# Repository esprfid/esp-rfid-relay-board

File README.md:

# ESP-RFID Relay Board

This project is follow up for "ESP-RFID Board" but with few more options.

&nbsp;&nbsp;

## What is ESP-RFID Relay Board?
ESP-RFID Relay Board is tiny ESP12 module (ESP8266) board, designed with wiegand RFID readers in mind and [ESP-RFID Firmware](https://github.com/esprfid/esp-rfid)

* Small size factor, sometimes possible to glue it into existing readers.
* Single power source to power 12V/2A powers ESP12 module, RFID Wiegand Reader and magnetic lock for opening doors.
* Exposed programming pins for ESP8266
* Due to interesting hardware design, you get multiple possible setup options:
  * Forward Bell ringing on reader to MCU or pass it out of board
  * Track Door Status
  * Control reader’s status LED
  * Control reader’s status BUZZER sound
  * Power reader, lock and the board through single 12V, 2A PSU
  * Optionally power magnetic lock through external AC/DC PSU
  * Possible to use any kind and any type of wiegand readers
  * Enables you to make IOT Access System with very litle wiring
  * Fit in universal enclosures with DIN mount
* Opensource Hardware/Cloud RFID reader/Wifi RFID reader

## Wiring example:

&nbsp;&nbsp;

## RESET and FLASH Buttons
Same as for any other ESP8266 programmer where you need to put EPS8266 into a specific mode. If you want to upload your program, you would use this buttons to put ESP8266 into FLASH mode. Check programming procedure down.

## Reader 9 pin terminal
The reason for 9 pins is to cover the most complex wiegand reader i could fins on the market. Mostly they only have 5 or 6 wires but sometimes, they also have 9 wire versions.

**PINNAME**|**CONNECTION**|**DESCRIPTION**
:-----|:-----|:-----
**DO**|GPIO4|Wiegand data line **D0** (*)
**D1**|GPIO5|Wiegand data line **D1**. (*)
**WG**|GPIO0|Some readers have WG line which if HIGH/LOW can change Wiegand stream bits. Usually not very important!
**BUZ**|GPIO12|Almost always Wiegand RFID Readers have Buzzer line which can control piezo buzzer. Due to some inconsistency among readers, i was able to make it work only when i connect this line through 10K resistor and than control it with changing HIGH/LOW on that particular pin, depending what i want. IMPORTANT: **P3** Pad on the back of board, can make that line to be connected directly to GPIO or through 10k resistor. Check **P3** Pad explanation.
**LED**|GPIO15|Most Wiegand readers have RED/GREEN status LEDs. Some color is default and if the line is changed HIGH/LOW than the other color appears.
**GND**|GND|Planned for Wiegand RFID Reader GND.
**VIN**|VIN|Connected directly to board’s POWER terminal’s positive pole. (*)
**F2**|To BTN/IN terminal left pole or to  GPIO14 (**)|Rarely Wiegand RFID Readers incorporate one button which is often doorbell switch, but the version that i took as an example for this board has those wires. It’s simply the switch between F1/F2.
**F1**|To BTN/IN terminal right pole or to GPIO14 (**)|

## Screw Terminals On the bottom of ESP-RFID Relay Board

**TERMINAL NAME**|**DESCRIPTION**
:-----|:-----
**RPOW**|In case **RELAY-POWER** pad is connected, when relay connects the circuit, this terminal provides input voltage directly on it’s poles. So the door magnet lock can be powered directly through this terminal.
**RSW**|Since i used small signal relay, it had two sides so another side is also connecting at the same time when relay makes connection but it only cut circuit. So practical use for this terminal can be to power magnetic lock with external source and even AC so that you get buzzing sound when the lock opens and avoid jamming of the lock. (*)
**POWER 8V-12V**|This is the main power source and in some settings only power source that you need. Please provide minimum 2A if you also power magnetic lock and Wiegand RFID Reader from same source, through ESP-RFID Relay Board
**DOORSTAT**|This terminal was planned to accept door status magnet switch. It can be also repurposed since it’s just a "button" connected to **GPIO16**.
**BTN/IN**|Depending on **P1** and **P2** Pads connection, it can have different purposes.Check **P2/P3** pads description below.

## Configuration pads P1, P2, P3, RELAY-POWER, 5V/3V3

**PAD NAME**|**DESCRIPTION**
:-----|:-----
**P1**|**Options:** Connected poles **3** and **2** redirects **F1** on **RFID Reader Terminal** to **BTN/IN** right pole. Connected poles 3 and 1 and you will get **GPIO14** to be connected on left **BTN/IN** terminal, grounded with 10k resistor. Connected poles **2** and **1** and you will power pin **F1** on **RFID Reader Terminal** with **GPIO14** (*)
**P2**|**Options:** Connected poles **3** and **2** redirects **F2** on  RFID Reader Terminal to BTN/IN left pole. Connected poles 3 and 1 and you will get 3V3 on left pin of BTN/IN terminal. Connected poles **2** and **1** and you will power pin **F2** on **RFID Reader Terminal** with 3V3 (*)
**P3**|**Options:** Connected poles **1** and **2** redirects **BUZ** pin on **RFID Reader Terminal** and **GPIO12**. Connected poles **2** and **3** redirects **BUZ** pin on **RFID Reader Terminal** and **GPIO12** through 10K resistor.
**RELAY-POWER**| This pad is usually connected if you want to power **RPOW** Terminal from main power source as **ESP-RFID Relay Board**
**5V/3V3**|Only purpose of this pad is to connect 5V or 3V3 line to **PROG’s** **POW** pin.

## Pads and what was the idea.
The main idea was to be able to adjust this little board to your scenario and also not  to occupy few GPIO where there is possibility to use those in some other way.

For example, i thought that somebody would like to have remote doorbell but somebody would simple hook it directly. Yet, it might happen that you don’t need doorbell at all but you might find use for GPIO14. So, i made custom PCB Three Way Pad.

&nbsp;&nbsp;

Find out about it here:  
https://hackaday.io/project/54277-3-way-pcb-pad  
https://github.com/nardev/eagle3wayPCBpads  
So, it’s similar to other pads which you just solder but this pad has unique shape so it can be soldered not in 2 but in 3 different ways. Just solder it in a way you want. (*) Check the table with description above.

**P1 and P2** pads must be set in pair. Essentially you can get one of three different options.  
**I** : You can redirect F1 and F2 on RFID Reader Terminal to BTN/IN terminal.  
**II**: You can redirect input on F1 and F2 on RFID Reader Terminal to ESP8266’s GPIO14.  
**III**: You can redirect BTN/IN terminal to ESP8266’s GPIO14 as button input.  

**P3** has bit strange purpose. I noticed that most popular wiegand readers have BUZZER line which i couldn’t control directly by simply HIGH/LOW on digital pins of ESP8266 and i also couldn’t  find any docs what signal is required, but i found a way for most of readers, it’s simply to put 10K resistor on the line. But, since it varies i also left an option to hook it directly to GPIO12  

**RELAY-POWER** is just connecting positive line to RPOW terminal. Usually, if you power the lock from the ESP-RFID Relay Board, that pad will be connected and you will use RPOW terminal to hook the lock.  

**5V/3V3** pad can be handy if you are powering ESP12F module through programmer itself while programming.  

## Relay
The relay used on this board is HFD4/5, DPST signal relay and it’s controlled through **GPIO13** on ESP8266.

## PROGRAMMING
#### Programming procedures and options.

**ESP-RFID relay Board**​ is essentially dev board extension for **ESP12​** modules. As that, it has **RESET​** and **FLASH​** buttons and the rest of circuit required to put ESP8266 in programming mode.
In order to program the board, you would need **"USB-TTL​"** or similar compatible programmer. (I personally like this 1$ one ​[here​](https://www.electrodragon.com/product/usb-ttl-serial-ch340-board/))

**Programming Procedure**

Considering that you already installed required drivers for your OS and that you have programming software already set, follow procedure:
1. Connect your **USB-TTL​** programmer to P ROG​ terminal. (Don’t forget to cross lines, RX to TX and vice versa)
2. Press **FLASH​** and **RESET​** buttons together.
3. Release **RESET​** Button and keep **FLASH​** Button pressed for 1-2 sec and than release it too.
4. Now, your ESP8266​ should be in **FLASH​** mode and you can upload you program.
(*) I noticed that it it doesn’t make any problems if you keep **FLASH​** Button pressed and sometimes **ESP8266​** won’t start with ​**FLASH​** mode in any other way.

## KNOWN ISSUES
* Silkscreen mistake WG/LED pins should be switched. (To test with base
firmware and setting pins to down/up and to check if that is the case only with
ESP-RFID​ firmware)

* Sometimes, connected ringing button through board, VAC source and to bell,
causes buck converter to jamm. It could be due to poor wire quality or something
else. But usually if it doesn’t occur immediately on first try, it never appears later.

## Short video walk-through

### You can get this board from my Tindie shop:

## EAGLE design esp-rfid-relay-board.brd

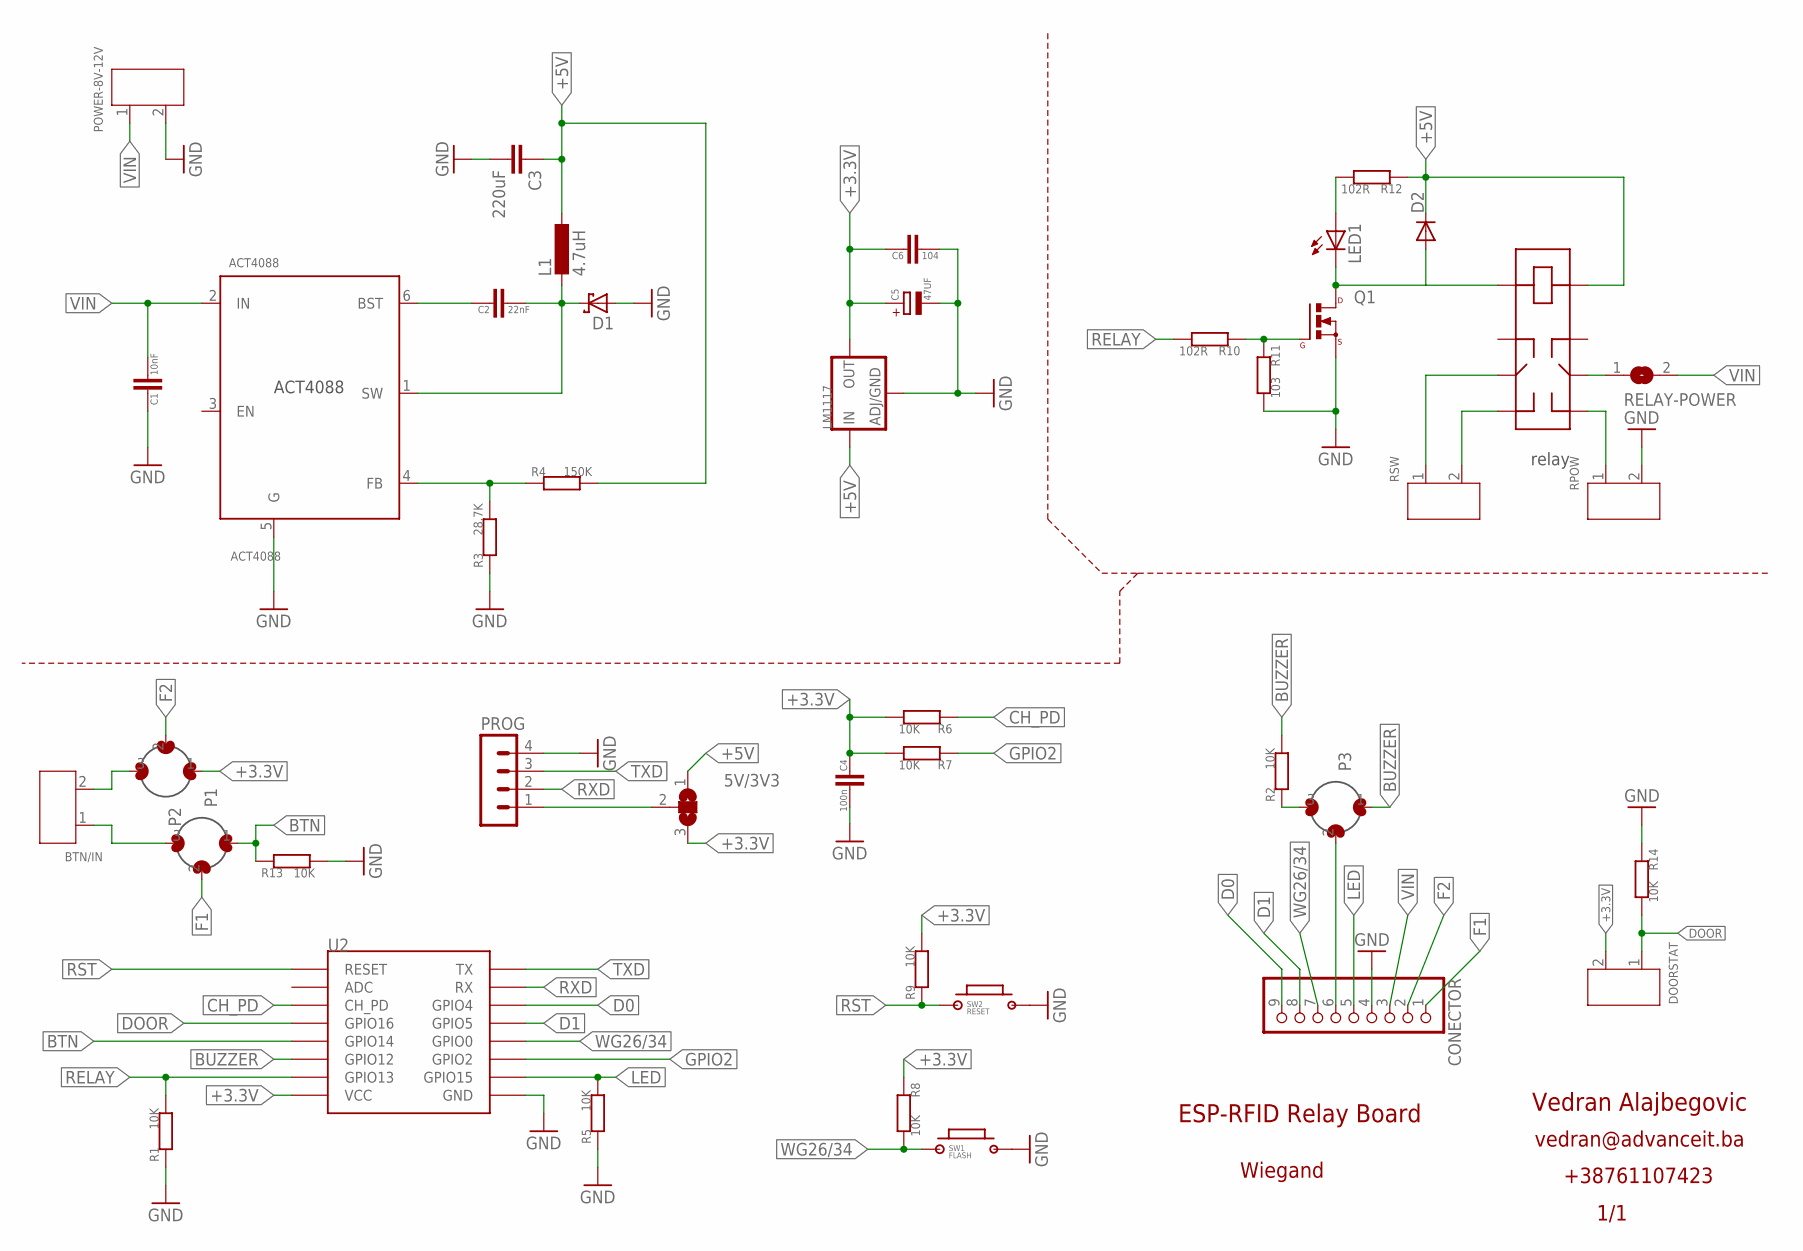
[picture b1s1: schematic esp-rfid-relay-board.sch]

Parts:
5V/3V3: SJ2W; SJ_2
ACT4088: ACT4088; SOT-23-6
BTN/IN: SCREW-TERMINAL-GREEN(2P-3.5); H2-3.5-7.0X7.0MM
C1: 10nF; C_0805
C2: 22nF; C_0805
C3: 220uF; C1210
C4: 100n; C_0805
C5: 47UF; CPOL_B3528
C6: 104; C_0805
CONECTOR: PINHD-1X9; 1X09
D1: SCHOTTKY-DIODESMD; SMB
D2: 4007-4148; DIO_SOD123FL
DOORSTAT: SCREW-TERMINAL-GREEN(2P-3.5); H2-3.5-7.0X7.0MM
L1: 4.7uH; L3225M
LED1: LED0805LED; 0805LED
LM1117: POWERSOT223; SOT223
P1, P2, P3: SJ3; SJ_3
POWER-8V-12V: SCREW-TERMINAL-GREEN(2P-3.5); H2-3.5-7.0X7.0MM
PROG: MA04-1
Q1: MOSFET_NSOT23; SOT23
R1, R2, R5, R6, R7, R8, R9, R13, R14: 10K; R_0805
R3: 28.7K; R_0805
R4: 150K; R_0805
R10, R12: 102R; R_0805
R11: 103; R_0805
RELAY: 2XSWITCH; HFD3-SIGNAL
RELAY-POWER: SJ
RPOW: SCREW-TERMINAL-GREEN(2P-3.5); H2-3.5-7.0X7.0MM
RSW: SCREW-TERMINAL-GREEN(2P-3.5); H2-3.5-7.0X7.0MM
SW1: FLASH; 2P-SWITCH-TURTLE
SW2: RESET; 2P-SWITCH-TURTLE
U2: ESP12SMD; ESP12-SMD

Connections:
+3.3V: 5V/3V3.3, C4.1, C5.+, C6.1, DOORSTAT.2, LM1117.OUT1 (OUT), LM1117.OUT2 (OUT), P2.1, R6.2, R7.2, R8.1, R9.2, U2.VCC
+5V: 5V/3V3.1, C3.1, D2.C, L1.1, LM1117.IN+ (IN), R4.2, R12.1, RELAY.8
BTN: P1.1, R13.1, U2.GPIO14
BUCK1: ACT4088.1 (SW), C2.2, D1.C, L1.2
BUCK2: ACT4088.4 (FB), R3.2, R4.1
BUCK3: ACT4088.6 (BST), C2.1
BUZZER: P3.1, R2.2, U2.GPIO12
CH_PD: R6.1, U2.CH_PD
D0: CONECTOR.9, U2.GPIO4
D1: CONECTOR.8, U2.GPIO5
DOOR: DOORSTAT.1, R14.2, U2.GPIO16
F1: CONECTOR.1, P1.2
F2: CONECTOR.2, P2.2
GND: ACT4088.5 (G), C1.1, C3.2, C4.2, C5.-, C6.2, CONECTOR.4, D1.A, LM1117.GND, POWER-8V-12V.2, PROG.4, Q1.2 (S), R1.1, R3.1, R5.1, R11.2, R13.2, R14.1, RPOW.2, SW1.2, SW2.2, U2.GND
GPIO2: R7.1, U2.GPIO2
LED: CONECTOR.5, R5.2, U2.GPIO15
unnamed: 5V/3V3.2, PROG.1
unnamed: RELAY.6, RELAY-POWER.1
unnamed: RELAY.5, RPOW.1
unnamed: RELAY.4, RSW.2
unnamed: BTN/IN.1, P1.3
unnamed: BTN/IN.2, P2.3
unnamed: RELAY.3, RSW.1
unnamed: CONECTOR.6, P3.2
unnamed: P3.3, R2.1
RELAY: R1.2, R10.2, U2.GPIO13
RELN1: Q1.1 (G), R10.1, R11.1
RELN2: D2.A, LED1.C, Q1.3 (D), RELAY.1
RELN4: LED1.A, R12.2
RST: R9.1, SW2.1, U2.RESET
RXD: PROG.2, U2.RXD0 (RX)
TXD: PROG.3, U2.TXD0 (TX)
VIN: ACT4088.2 (IN), C1.2, CONECTOR.3, POWER-8V-12V.1, RELAY-POWER.2
WG26/34: CONECTOR.7, R8.2, SW1.1, U2.GPIO0

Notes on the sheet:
relay
Wiegand
Vedran Alajbegovic
vedran@advanceit.ba
+38761107423
ESP-RFID Relay Board
1/1

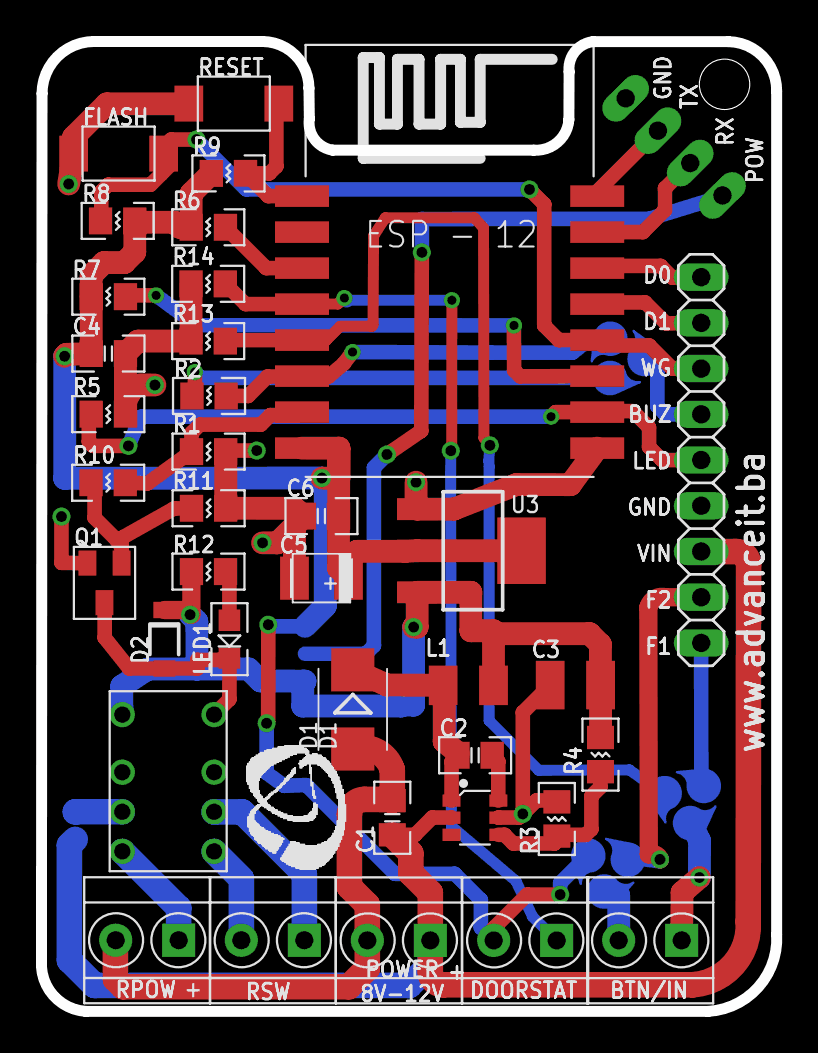
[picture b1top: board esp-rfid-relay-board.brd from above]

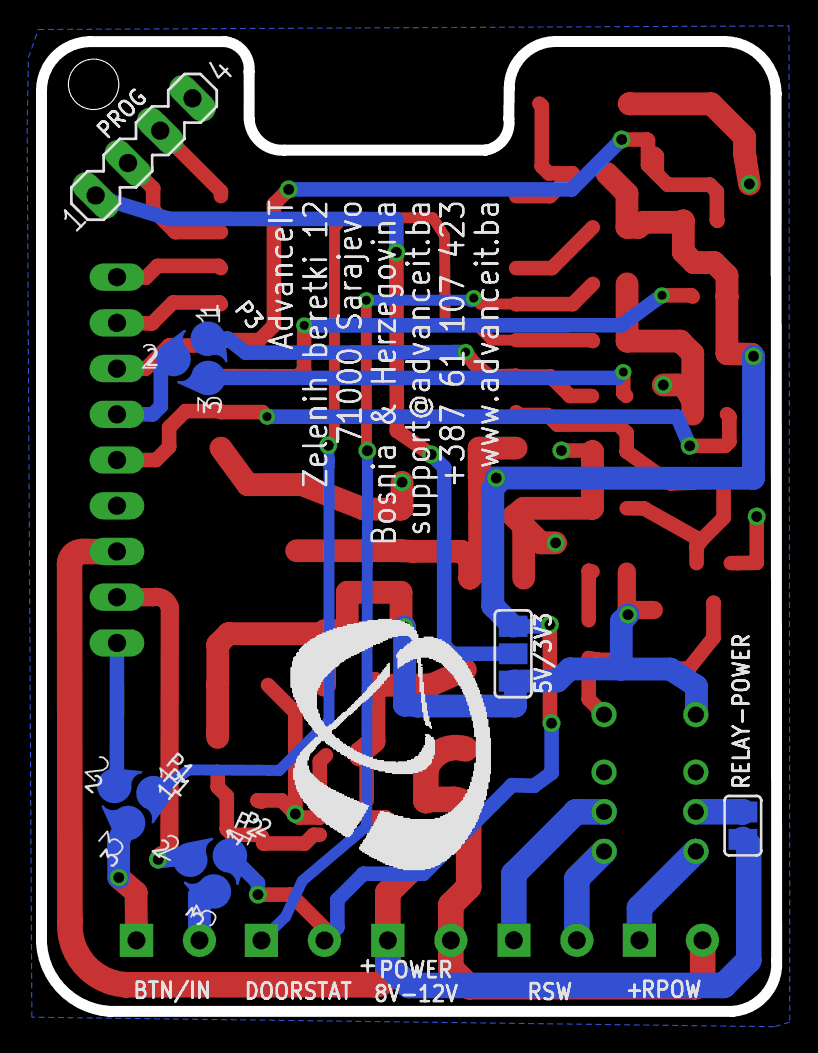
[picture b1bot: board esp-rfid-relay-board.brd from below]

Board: 2 copper layers, 40.8 x 53.9 mm, 43 parts (6 on the bottom side), 34 nets.

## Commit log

2018-09-25 images
2018-09-25 readme
2018-09-26 tindie url

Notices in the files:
parts and their libraries:
SparkFun-Aesthetics: Licensing: Creative Commons ShareAlike 4.0 International - https://creativecommons.org/licenses/by-sa/4.0
